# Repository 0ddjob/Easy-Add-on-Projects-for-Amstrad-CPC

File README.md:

# Easy Add on Projects for Amstrad CPC
 Hardware projects from the book by Owen Bishop.

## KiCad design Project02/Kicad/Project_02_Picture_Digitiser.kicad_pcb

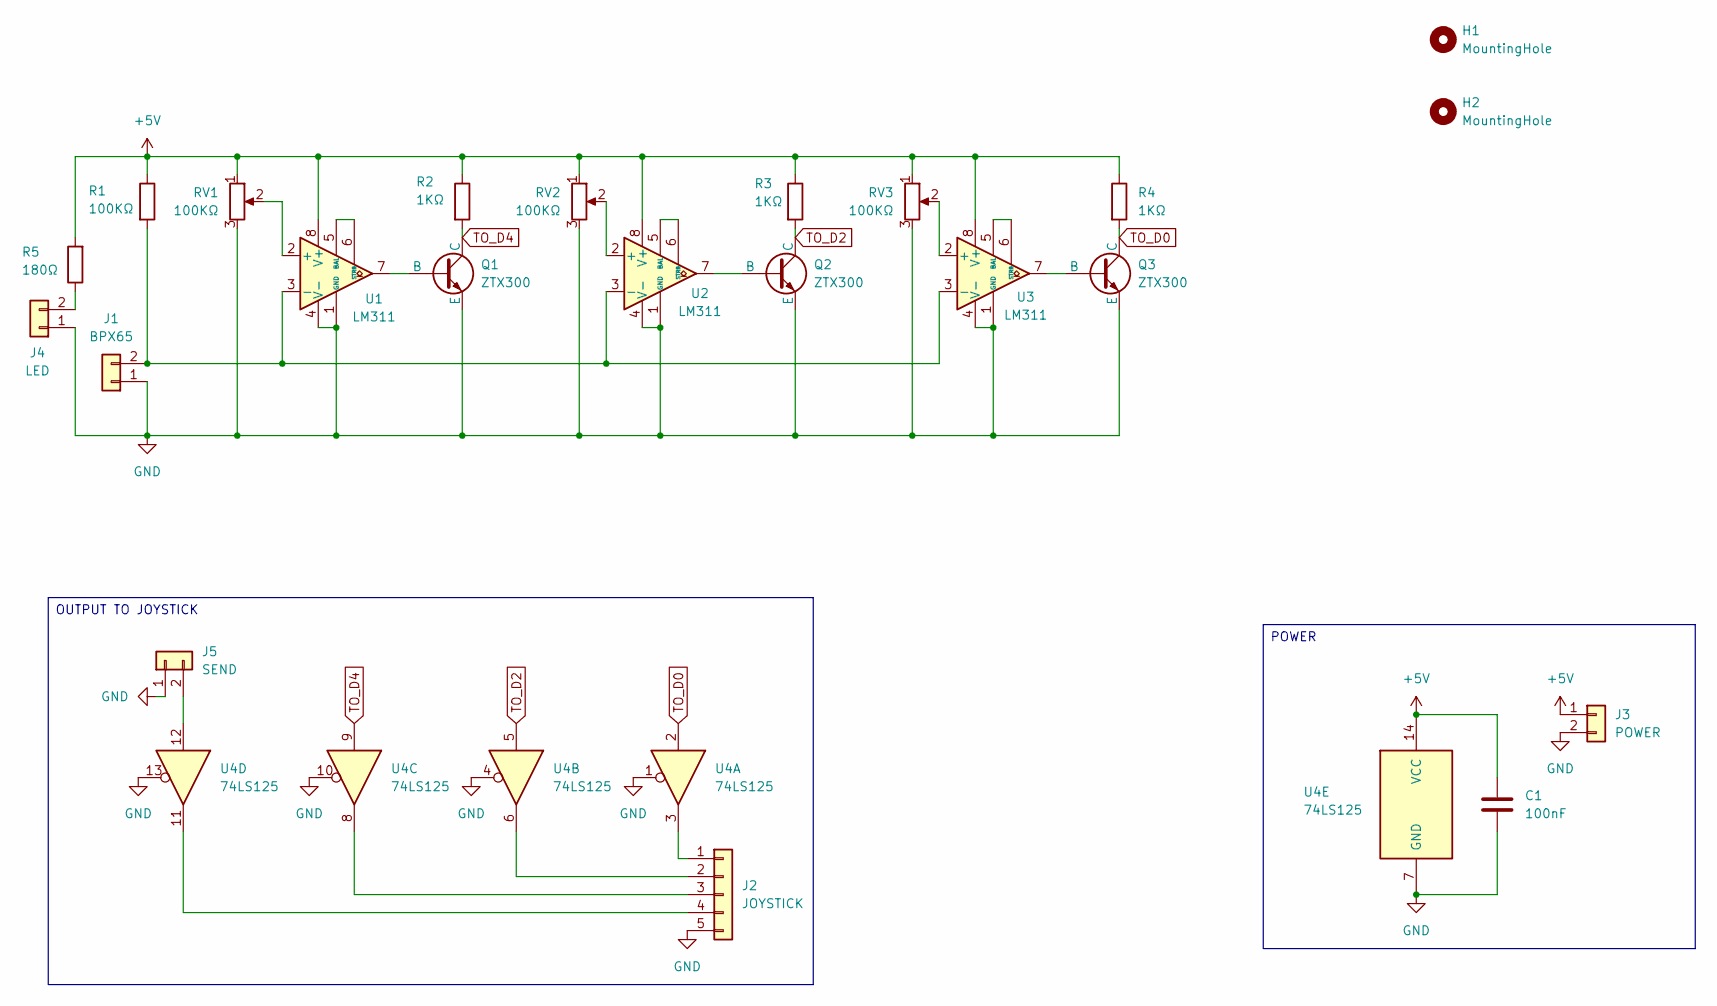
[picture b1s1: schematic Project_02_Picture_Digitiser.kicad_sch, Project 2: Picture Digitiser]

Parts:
C1: 100nF; C_Disc_D3.4mm_W2.1mm_P2.50mm
H1, H2: MountingHole; MountingHole_3.2mm_M3
J1: BPX65; PinSocket_1x02_P2.54mm_Vertical
J2: JOYSTICK; PinSocket_1x05_P2.54mm_Vertical
J3: POWER; PinSocket_1x02_P2.54mm_Vertical
J4: LED; PinSocket_1x02_P2.54mm_Vertical
J5: SEND; PinSocket_1x02_P2.54mm_Vertical
Q1, Q2, Q3: ZTX300; TO-92_Inline
R1: 100KΩ; R_Axial_DIN0207_L6.3mm_D2.5mm_P7.62mm_Horizontal
R2, R3, R4: 1KΩ; R_Axial_DIN0207_L6.3mm_D2.5mm_P7.62mm_Horizontal
R5: 180Ω; R_Axial_DIN0207_L6.3mm_D2.5mm_P7.62mm_Horizontal
RV1, RV2, RV3: 100KΩ; Potentiometer_Bourns_3296W_Vertical
U1, U2, U3: LM311; DIP-8_W7.62mm
U4: 74LS125; DIP-14_W7.62mm

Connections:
+5V: C1.1, J3.1, R1.1, R2.1, R3.1, R4.1, R5.2, RV1.1, RV2.1, RV3.1, U1.8 (V+), U2.8 (V+), U3.8 (V+), U4.14 (VCC)
GND: C1.2, J1.1, J2.5, J3.2, J4.1, J5.1, Q1.3 (E), Q2.3 (E), Q3.3 (E), RV1.3, RV2.3, RV3.3, U1.1 (GND), U1.4 (V-), U2.1 (GND), U2.4 (V-), U3.1 (GND), U3.4 (V-), U4.1, U4.4, U4.7 (GND), U4.10, U4.13
unnamed: J1.2, R1.2, U1.3 (-), U2.3 (-), U3.3 (-)
unnamed: J2.1, U4.3
unnamed: J2.2, U4.6
unnamed: J2.3, U4.8
unnamed: J2.4, U4.11
unnamed: J4.2, R5.1
unnamed: J5.2, U4.12
unnamed: Q1.2 (B), U1.7
unnamed: Q2.2 (B), U2.7
unnamed: Q3.2 (B), U3.7
unnamed: RV1.2, U1.2 (+)
unnamed: U1.5 (BAL), U1.6 (STRB)
unnamed: RV2.2, U2.2 (+)
unnamed: U2.5 (BAL), U2.6 (STRB)
unnamed: RV3.2, U3.2 (+)
unnamed: U3.5 (BAL), U3.6 (STRB)
TO_D0: Q3.1 (C), R4.2, U4.2
TO_D2: Q2.1 (C), R3.2, U4.5
TO_D4: Q1.1 (C), R2.2, U4.9

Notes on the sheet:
POWER
OUTPUT TO JOYSTICK

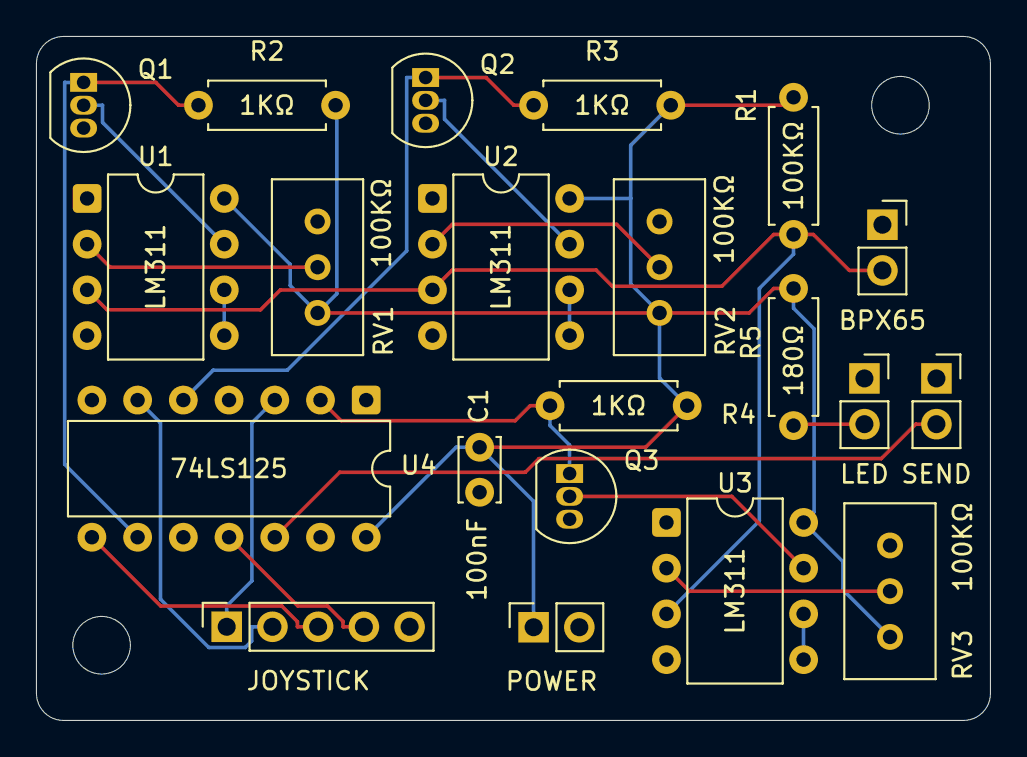
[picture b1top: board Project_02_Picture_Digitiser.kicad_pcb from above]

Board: 2 copper layers, 53.0 x 38.0 mm, 23 parts (0 on the bottom side), 21 nets.
